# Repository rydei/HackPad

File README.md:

Based on HackClub's MacroPad Guide.
https://hackpad.hackclub.com/guide

----------------------------------
File Structure:- 

--3D Model

  -HackPad with PCB.3mf
  
  -HackPad without PCB.3mf
  
--Firmware

  -hackpad_default.uf2
  
--MacroPadPackage(packages for the footprints and schematics)

--Schem and PCB Resources

  -hackpad.kicad_pro
  
----------------------------------
Schematic:-

PCB:-

Case with Lid:-

Case without Lid:-

BOM:-

-1x XIAO RP2040

-1x EC11 Rotary Encoder

-1x 0.91" 128x32 OLED Display

-4x WS2812B LEDs

-7x 1N4148 DO-35 Diodes

-6x MX-style Switches

-6x DSA Keycaps

-6x M3x5x4 Heatset inserts

-4x M3x16mm SHCS Bolts

-2x M3x12mm SHCS Bolts

-1x Case (2 printed parts)
----------------------------------
Extra Stuff:-
i forgot to log my time.(is this the end of world? prolly not)

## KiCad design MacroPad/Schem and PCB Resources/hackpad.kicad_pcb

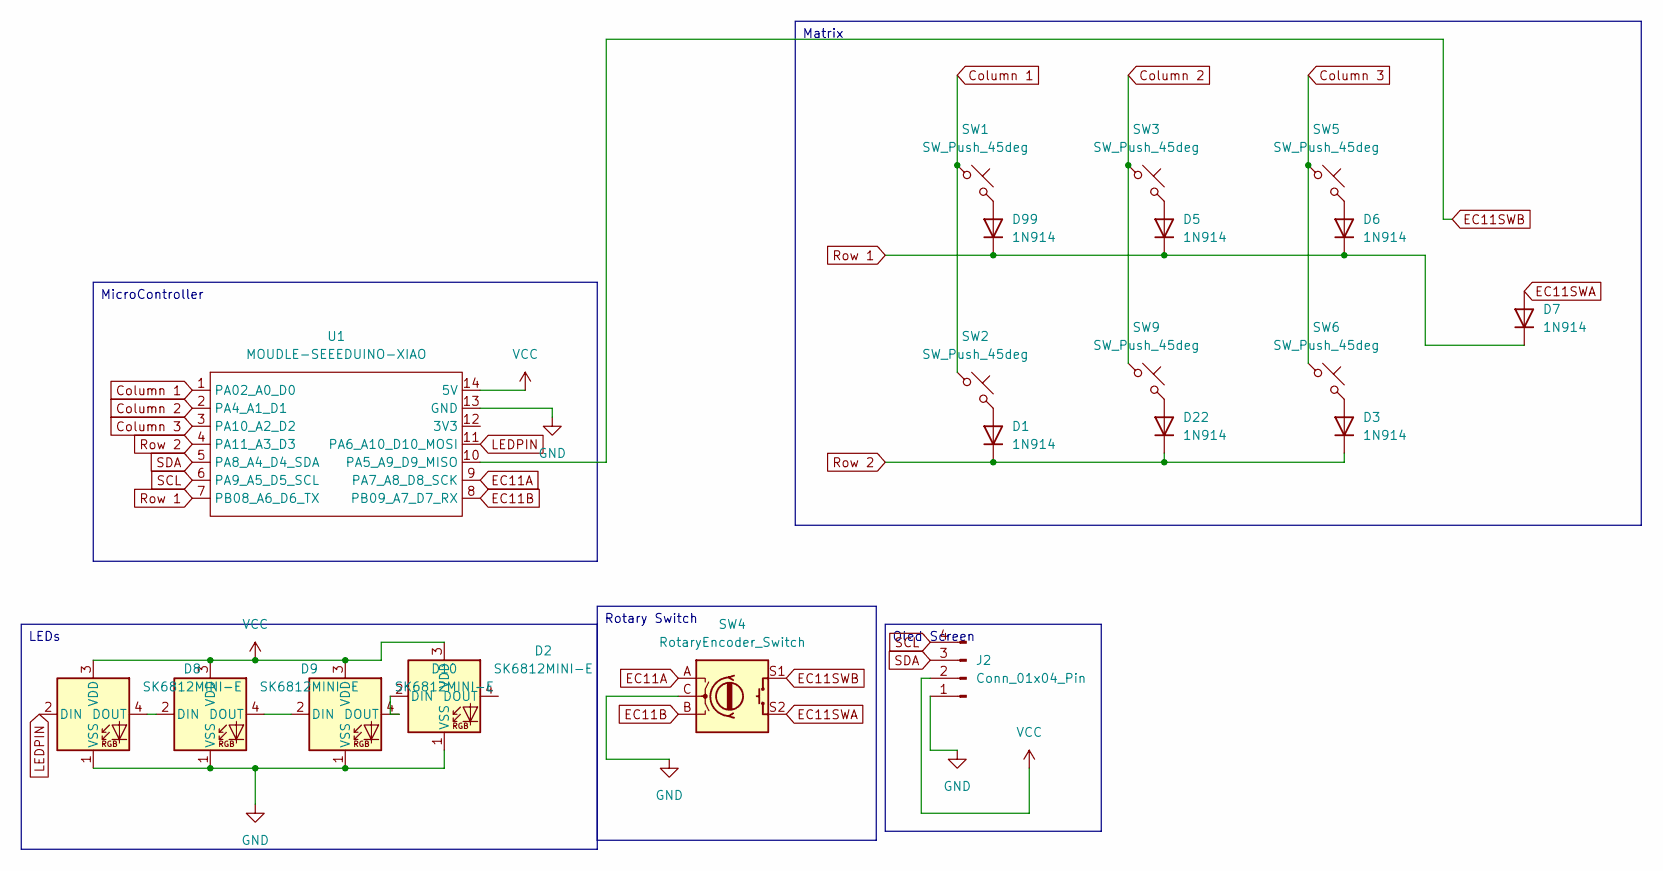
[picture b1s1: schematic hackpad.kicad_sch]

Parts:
D1, D3, D5, D6, D7, D22, D99: 1N914; D_DO-35_SOD27_P7.62mm_Horizontal
D2, D8, D9, D10: SK6812MINI-E; LED_SK6812MINI-E_3.2x2.8mm_P1.5mm_ReverseMount
J2: Conn_01x04_Pin; PinHeader_1x04_P2.54mm_Vertical
SW1, SW2, SW3, SW5, SW6, SW9: SW_Push_45deg; SW_Cherry_MX_1.00u_PCB
SW4: RotaryEncoder_Switch; RotaryEncoder_Alps_EC11E-Switch_Vertical_H20mm
U1: MOUDLE-SEEEDUINO-XIAO; XIAO-Generic-Hybrid-14P-2.54-21X17.8MM

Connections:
Column 1: SW1.1, SW2.1, U1.1 (PA02_A0_D0)
Column 2: SW3.1, SW9.1, U1.2 (PA4_A1_D1)
Column 3: SW5.1, SW6.1, U1.3 (PA10_A2_D2)
EC11A: SW4.A, U1.9 (PA7_A8_D8_SCK)
EC11B: SW4.B, U1.8 (PB09_A7_D7_RX)
EC11SWA: D7.2 (A), SW4.S2
EC11SWB: SW4.S1, U1.10 (PA5_A9_D9_MISO)
GND: D2.1 (VSS), D8.1 (VSS), D9.1 (VSS), D10.1 (VSS), J2.1, SW4.C, U1.13 (GND)
LEDPIN: D8.2 (DIN), U1.11 (PA6_A10_D10_MOSI)
unnamed: D1.2 (A), SW2.2
unnamed: D3.2 (A), SW6.2
unnamed: D5.2 (A), SW3.2
unnamed: D6.2 (A), SW5.2
unnamed: D8.4 (DOUT), D9.2 (DIN)
unnamed: D9.4 (DOUT), D10.2 (DIN)
unnamed: D2.2 (DIN), D10.4 (DOUT)
unnamed: D22.2 (A), SW9.2
unnamed: D99.2 (A), SW1.2
Row 1: D5.1 (K), D6.1 (K), D7.1 (K), D99.1 (K), U1.7 (PB08_A6_D6_TX)
Row 2: D1.1 (K), D3.1 (K), D22.1 (K), U1.4 (PA11_A3_D3)
SCL: J2.4, U1.6 (PA9_A5_D5_SCL)
SDA: J2.3, U1.5 (PA8_A4_D4_SDA)
VCC: D2.3 (VDD), D8.3 (VDD), D9.3 (VDD), D10.3 (VDD), J2.2, U1.14 (5V)

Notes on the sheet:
Oled Screen
LEDs
Matrix
Rotary Switch
MicroController

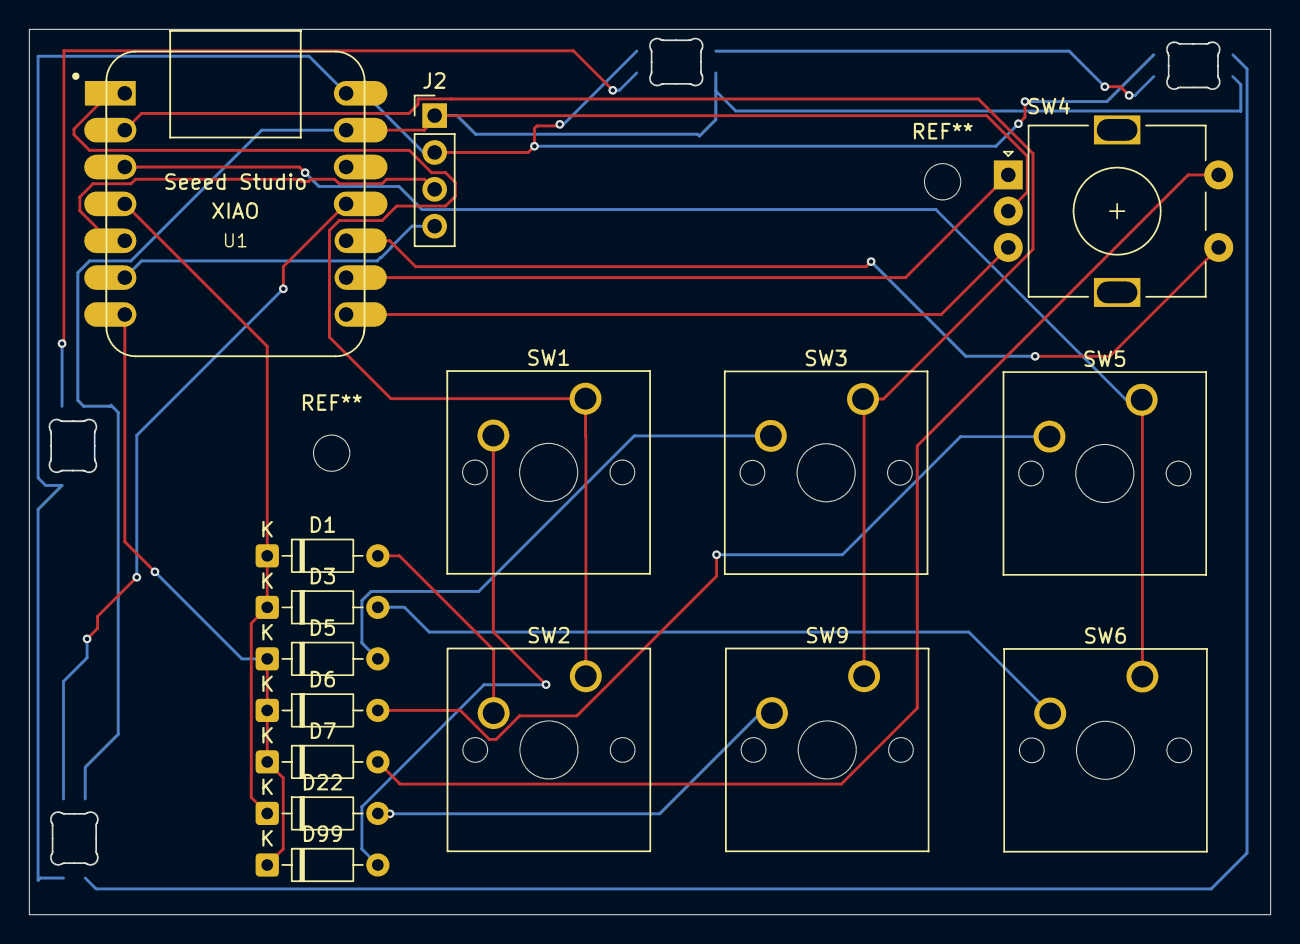
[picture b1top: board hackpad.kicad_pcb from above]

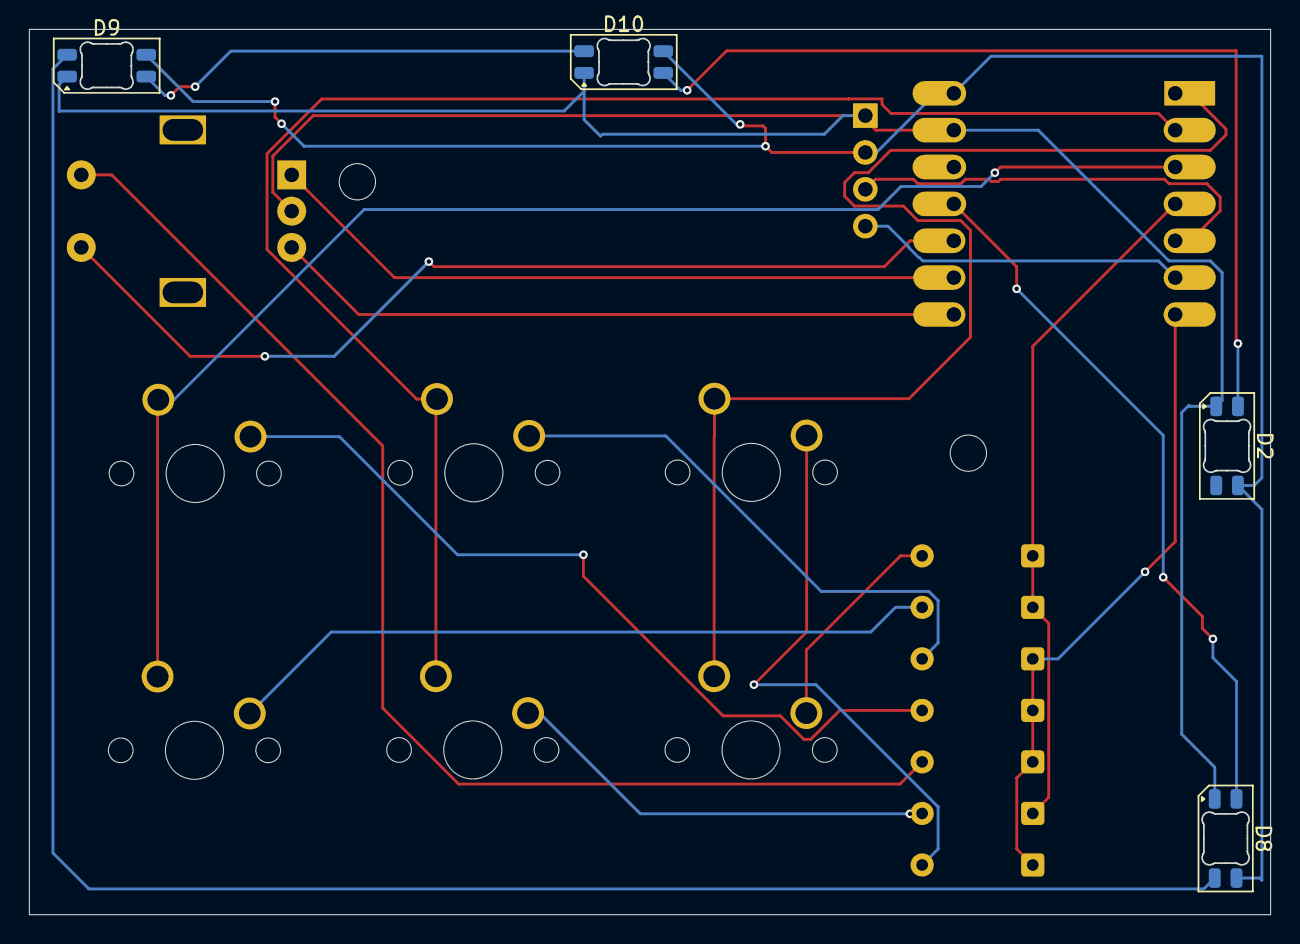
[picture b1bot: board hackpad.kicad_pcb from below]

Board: 2 copper layers, 85.5 x 61.0 mm, 20 parts (4 on the bottom side), 23 nets.

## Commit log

2026-06-05 made the schematic myself
2026-06-06 fixed the schematics
2026-06-06 Completed the pcb and added 2 extra leds in the schematic !
2026-06-06 Completed the PCB and added 2 extra leds!
2026-06-06 Finalized the PCB and Exported the 3D Model.
2026-06-06 Add files via upload
    Finished with the Project! (hope so)
2026-06-06 Add files via upload
    fixed the 3d model 🫠
2026-06-10 Add files via upload
    fixed the pcb errors.
